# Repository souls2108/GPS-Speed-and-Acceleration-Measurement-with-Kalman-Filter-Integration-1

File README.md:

# GPS-Speed-and-Acceleration-Measurement-with-Kalman-Filter-Integration
 GPS-based system for accurately measuring speed and acceleration, applying Kalman filtering techniques for enhanced precision. The system further includes a user-friendly OLED display for real-time speed visualization.

### Description:

GPS Speedometer project repository: This open-source project aims to provide a comprehensive GPS-based system for accurately measuring speed and acceleration, applying Kalman filtering techniques for enhanced precision. The system further includes a 1.5 inch OLED display for real-time speed visualization and a web interface for remote monitoring.<b>This project was implemented to measure vehicle telemetry for Team Firebolt Racing in mBAJA 2024 (SAEINDIA).</b>

### Hardware used:
<ol>
 <li>ublox NEO-6M</li>
 <li><a href="https://robu.in/product/gps-glonass-gnss-antenna-for-raspberry-pi-hat-and-arduino-shield-with-3-meter-cable/?gad_source=1&gclid=CjwKCAiA9ourBhAVEiwA3L5RFgNR95wsRVnACjbRkYZ2RfMn0eCl59X-f6alDHBtyXvHmg76V53xPRoCONcQAvD_BwE">GPS antenna (for better performance)</a></li>
 <li>BNO085 9DoF (accelerometer, gyroscope, magnetometer)</li>
 <li>NodeMCU v1.0</li>
 <li>1.5 inch OLED display by Waveshare [SSD1327]</li>
</ol>

## Features:
## 1. GPS-Based Speed and Acceleration Measurement
Utilizing GPS data, the system accurately calculates and measures real-time speed and acceleration. The integration of GPS technology ensures reliable and precise location-based speed readings.

## 2. Kalman Filter Implementation
To enhance the accuracy of speed and acceleration measurements, a Kalman filter is applied. The Kalman filter optimally combines GPS data with accelerometer readings, resulting in more reliable and smoother speed values, particularly in scenarios with signal noise or intermittent GPS connectivity.

## 3. OLED Display
The project includes an OLED display to provide a convenient and intuitive interface for users to monitor their speed in real time. The display showcases clear and easily readable speed information, making it suitable for various applications, such as automotive or fitness devices.

## 4. Webpage Display
For remote monitoring and data visualization, the system features a web interface. Users can access a webpage that displays real-time speed information, allowing for convenient monitoring without the need for physical interaction with the OLED display. The web interface supports multiple devices, providing a flexible and accessible solution.

## Getting Started:
1. Clone the repository to your local machine.
2. Install the required dependencies mentioned in the documentation.
3. Make the required changes in configuration to GPS module using U - Center software.
4. Connect the GPS module, BNO085 and OLED display to NodeMCU to set-up. 
5. Upload the provided code to your microcontroller.
6. Access the web interface to monitor real-time speed remotely.

### Port Map
<ul>
  <li>OLED SCREEN</li>
   <ol>
    <li>VCC -> 3V</li>
    <li>GND -> GND</li>
    <li>DIN -> D7</li>
    <li>CLK -> D5</li>
    <li>CS -> D8</li>
    <li>DC -> D0</li>
    <li>RST -> D3</li>
   </ol>

  <li>BNO085</li>
   <ol>
    <li>VIN -> 3V</li>
    <li>GND -> GND</li>
    <li>SCL -> D1</li>
    <li>SDA -> D2</li>
    <li>P0 -> GND</li>
    <li>P1 -> GND</li>
   </ol>

   <li>GPS</li>
   <ol>
    <li>VCC -> 3V</li>
    <li>GND -> GND</li>
    <li>RX -> D4</li>
    <li>TX -> D6</li>
   </ol>
</ul>

## Contribution Guidelines:
Welcome for contributions to enhance and expand the capabilities of this GPS speedometer system. Feel free to submit bug reports, feature requests, or pull requests to help improve the project.

Thank you for choosing our GPS Speedometer project. We hope it proves to be a valuable tool for your speed measurement and monitoring needs!

## References
<ul>
 <li>
  <a href = "https://youtu.be/TwhCX0c8Xe0?si=p0fIQ2RGdnS_CM2-">GPS Configuration Reference</a>
 </li>
 <li>
  <a href="https://github.com/olikraus/u8g2.git">Library for OLED display</a>
 </li>
 <li>
  <a href = "https://github.com/adafruit/Adafruit_BNO08x.git">Library for BNO085</a>
 </li>
 <li>
  <a href="https://youtu.be/6M6wSLD-8M8?si=LIJLbGDBOQZDQuQw">Kalman Filter Basics</a>
 </li>
 <li>
  <a href="https://github.com/morrissinger/ESP8266-Websocket.git">ESP8266 Web Sockets</a>
 </li>
</ul>

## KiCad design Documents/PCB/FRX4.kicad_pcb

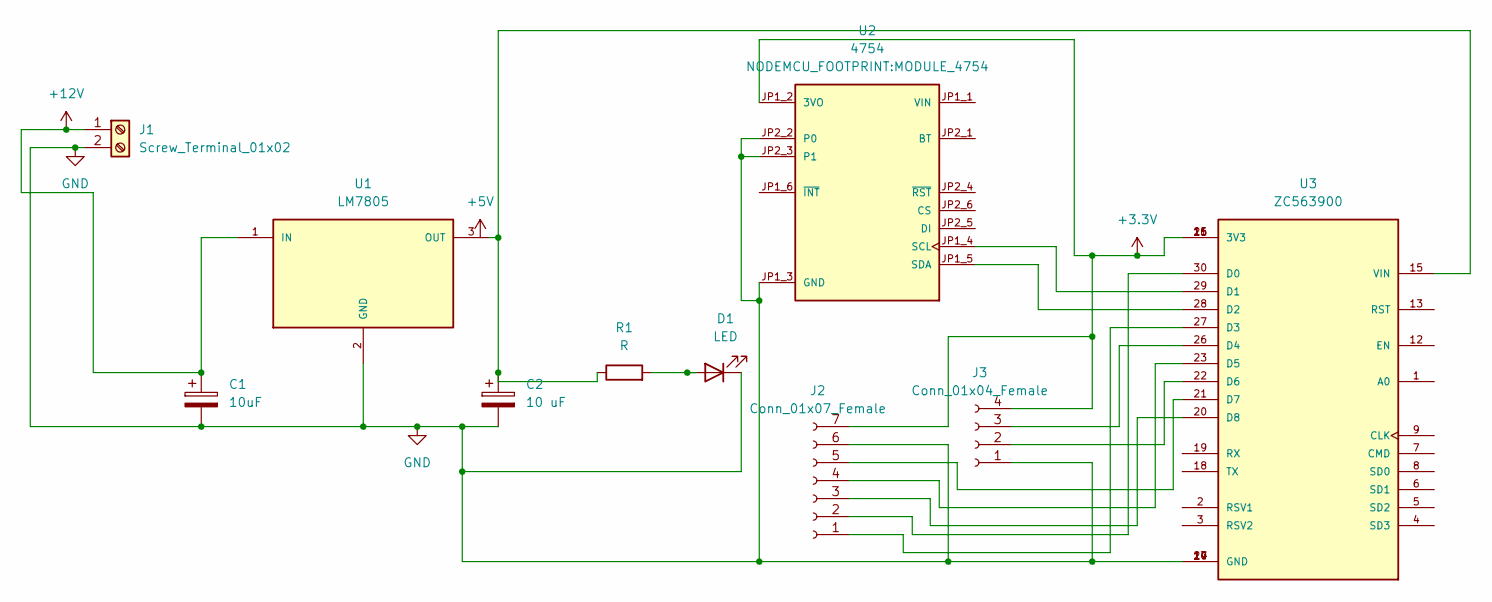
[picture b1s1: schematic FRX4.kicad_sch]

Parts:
C1: 10uF; CP_Radial_D10.0mm_P7.50mm
C2: 10 uF; CP_Radial_D10.0mm_P7.50mm
D1: LED; LED_D3.0mm_Horizontal_O3.81mm_Z10.0mm
J1: Screw_Terminal_01x02; TerminalBlock_bornier-2_P5.08mm
J2: Conn_01x07_Female; JST_EH_B7B-EH-A_1x07_P2.50mm_Vertical
J3: Conn_01x04_Female; PinHeader_1x04_P2.54mm_Vertical
R1: R; R_Axial_DIN0309_L9.0mm_D3.2mm_P12.70mm_Horizontal
U1: LM7805; TO220
U2: 4754; MODULE_4754; PARTREV 2021-03-16
U3: ZC563900; MODULE_ZC563900; PARTREV 1.0

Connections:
+3.3V: J2.7, J3.4, U2.JP1_2 (3VO), U3.11 (3V3), U3.16 (3V3), U3.25 (3V3)
+5V: C2.1, R1.1, U1.3 (OUT), U3.15 (VIN)
+12V: C1.1, J1.1, U1.1 (IN)
GND: C1.2, C2.2, D1.1 (K), J1.2, J2.6, J3.1, U1.2 (GND), U2.JP1_3 (GND), U2.JP2_2 (P0), U2.JP2_3 (P1), U3.10 (GND), U3.14 (GND), U3.17 (GND), U3.24 (GND)
unnamed: D1.2 (A), R1.2
unnamed: J2.1, U3.27 (D3)
unnamed: J2.2, U3.30 (D0)
unnamed: J2.3, U3.20 (D8)
unnamed: J2.4, U3.23 (D5)
unnamed: J2.5, U3.21 (D7)
unnamed: J3.2, U3.22 (D6)
unnamed: J3.3, U3.26 (D4)
unnamed: U2.JP1_4 (SCL), U3.29 (D1)
unnamed: U2.JP1_5 (SDA), U3.28 (D2)

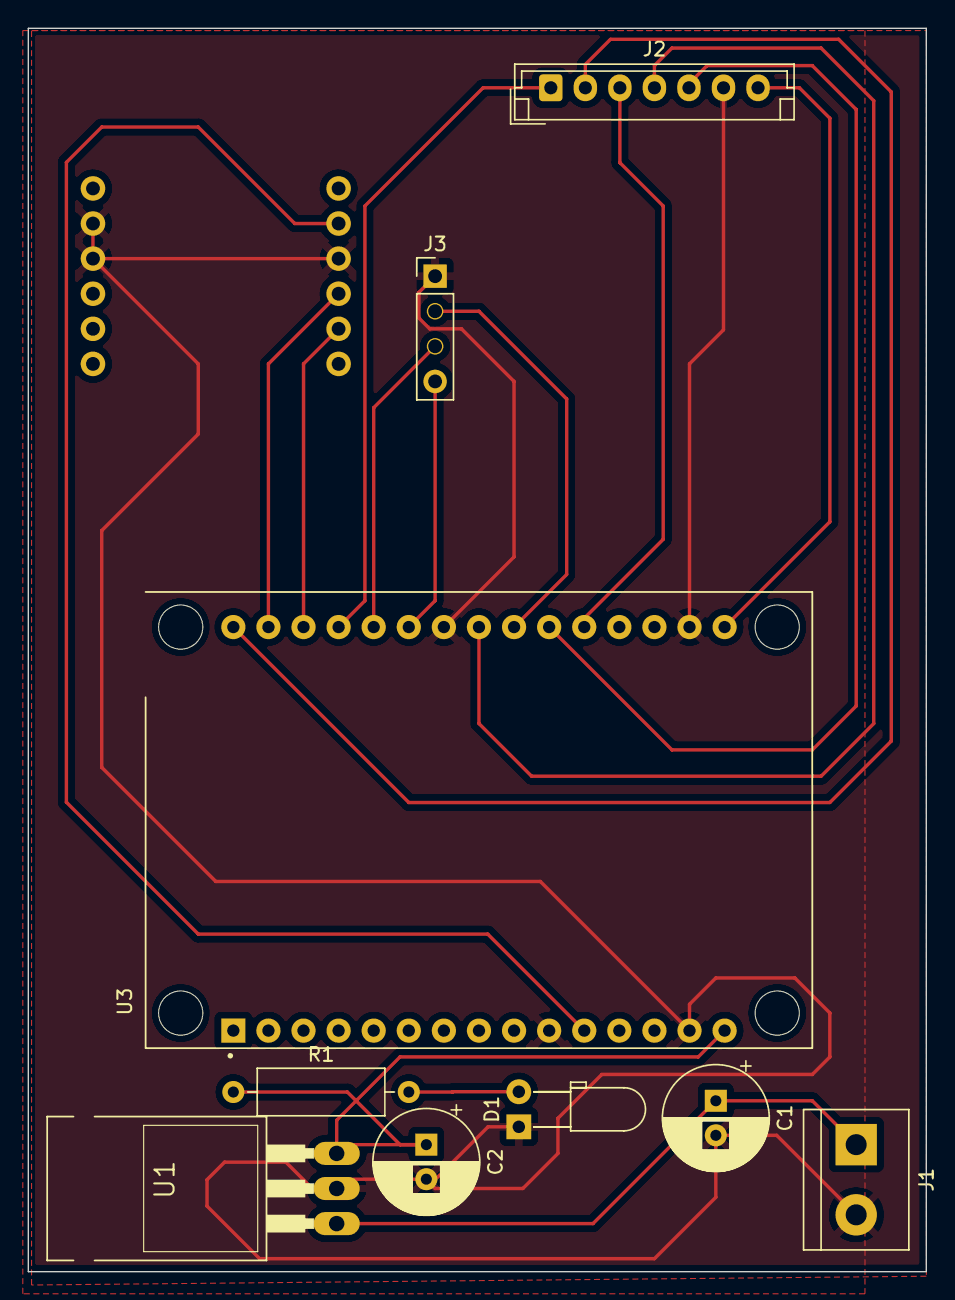
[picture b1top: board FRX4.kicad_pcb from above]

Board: 2 copper layers, 65.0 x 90.0 mm, 10 parts (1 on the bottom side), 14 nets.

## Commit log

2024-01-26 Updated README.md
    added hardware used section
2024-01-26 Update README.md
    Changes to hardware used section.
2024-02-01 Renamed files
